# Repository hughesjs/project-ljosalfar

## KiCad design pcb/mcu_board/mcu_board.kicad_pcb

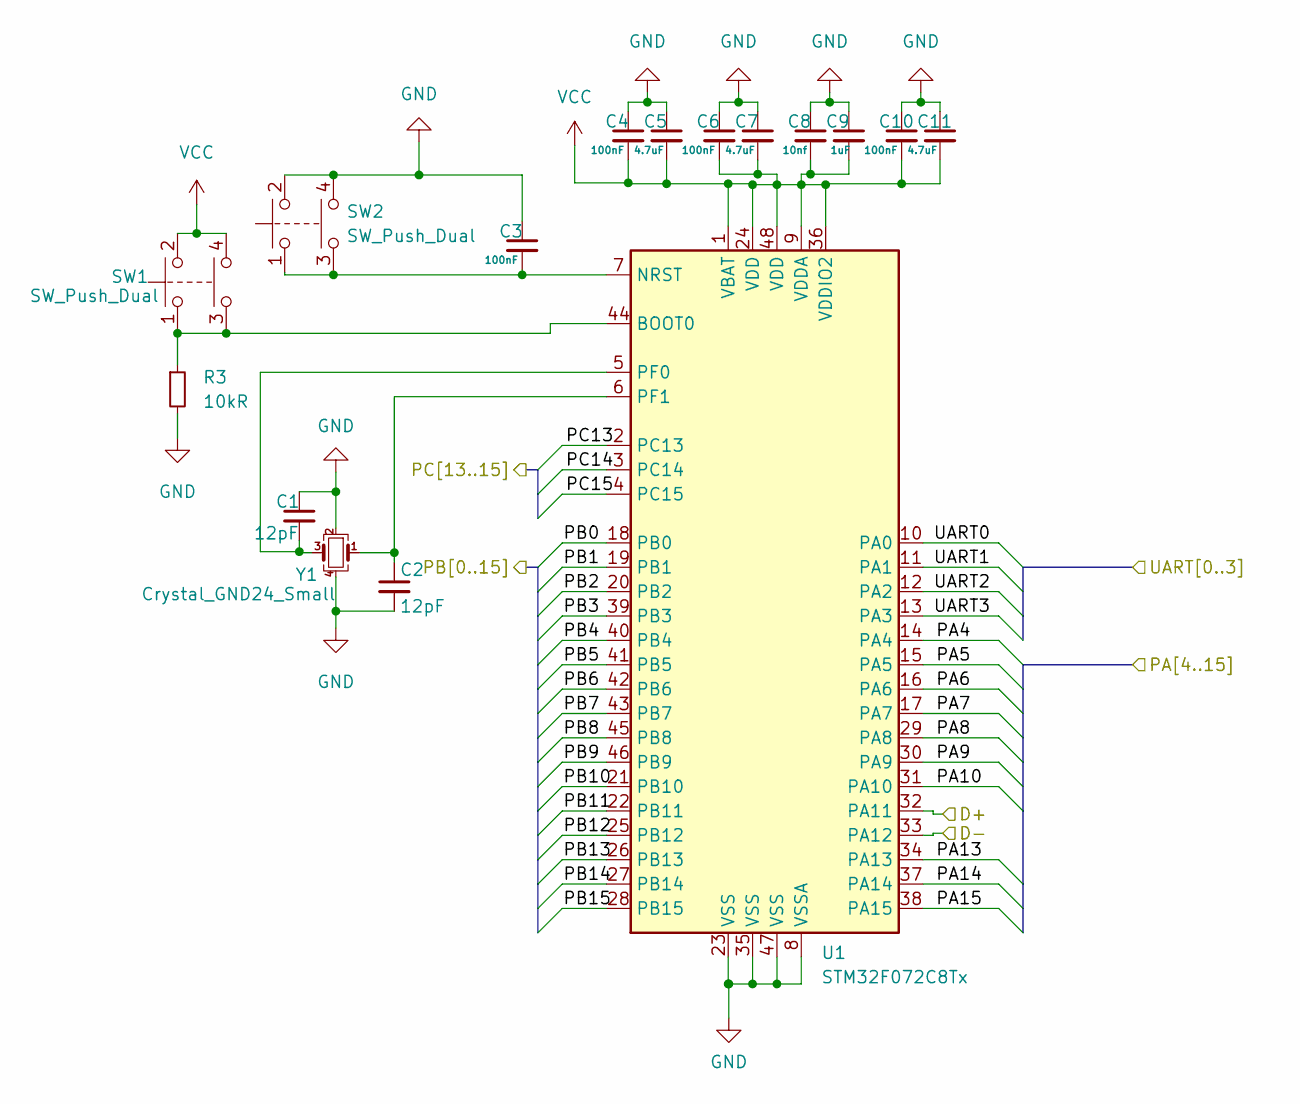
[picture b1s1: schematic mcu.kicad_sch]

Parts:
C1, C2: 12pF; C_0402_1005Metric
C3, C4, C6, C10: 100nF; C_0402_1005Metric
C5, C7, C11: 4.7uF; C_0603_1608Metric
C8: 10nf; C_0402_1005Metric
C9: 1uF; C_0603_1608Metric
R3: 10kR; R_0603_1608Metric
SW1, SW2: SW_Push_Dual; SW_TS-1187A-B-A-B
U1: STM32F072C8Tx; LQFP-48_7x7mm_P0.5mm
Y1: Crystal_GND24_Small; Crystal_SMD_3225-4Pin_3.2x2.5mm

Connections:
/USB_IN/D+: U1.32 (PA11); also elsewhere on the board
/USB_IN/D-: U1.33 (PA12); also elsewhere on the board
/mcu/PA4: U1.14 (PA4)
/mcu/PA5: U1.15 (PA5)
/mcu/PA6: U1.16 (PA6)
/mcu/PA7: U1.17 (PA7)
/mcu/PA8: U1.29 (PA8)
/mcu/PA9: U1.30 (PA9)
/mcu/PA10: U1.31 (PA10)
/mcu/PA13: U1.34 (PA13)
/mcu/PA14: U1.37 (PA14)
/mcu/PA15: U1.38 (PA15)
/mcu/PB0: U1.18 (PB0)
/mcu/PB1: U1.19 (PB1)
/mcu/PB2: U1.20 (PB2)
/mcu/PB3: U1.39 (PB3)
/mcu/PB4: U1.40 (PB4)
/mcu/PB5: U1.41 (PB5)
/mcu/PB6: U1.42 (PB6)
/mcu/PB7: U1.43 (PB7)
/mcu/PB8: U1.45 (PB8)
/mcu/PB9: U1.46 (PB9)
/mcu/PB10: U1.21 (PB10)
/mcu/PB11: U1.22 (PB11)
/mcu/PB12: U1.25 (PB12)
/mcu/PB13: U1.26 (PB13)
/mcu/PB14: U1.27 (PB14)
/mcu/PB15: U1.28 (PB15)
/mcu/PC13: U1.2 (PC13)
/mcu/PC14: U1.3 (PC14)
/mcu/PC15: U1.4 (PC15)
/mcu/UART0: U1.10 (PA0)
/mcu/UART1: U1.11 (PA1)
/mcu/UART2: U1.12 (PA2)
/mcu/UART3: U1.13 (PA3)
GND: C1.1, C2.2, C3.1, C4.1, C5.1, C6.1, C7.1, C8.1, C9.1, C10.1, C11.1, R3.2, SW2.2, SW2.4, U1.8 (VSSA), U1.23 (VSS), U1.35 (VSS), U1.47 (VSS), Y1.2, Y1.4; also elsewhere on the board
unnamed: C1.2, U1.5 (PF0), Y1.3
unnamed: C2.1, U1.6 (PF1), Y1.1
unnamed: C3.2, SW2.1, SW2.3, U1.7 (NRST)
unnamed: R3.1, SW1.1, SW1.3, U1.44 (BOOT0)
VCC: C4.2, C5.2, C6.2, C7.2, C8.2, C9.2, C10.2, C11.2, SW1.2, SW1.4, U1.1 (VBAT), U1.9 (VDDA), U1.24 (VDD), U1.36 (VDDIO2), U1.48 (VDD); also elsewhere on the board

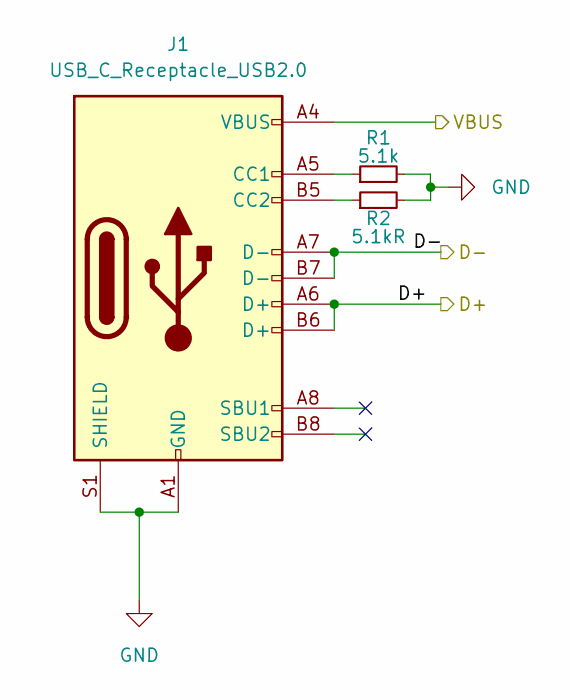
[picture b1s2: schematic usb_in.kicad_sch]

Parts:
J1: USB_C_Receptacle_USB2.0; USB_C_Receptacle_HRO_TYPE-C-31-M-12
R1: 5.1k; R_0603_1608Metric
R2: 5.1kR; R_0603_1608Metric

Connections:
/USB_IN/D+: J1.A6 (D+), J1.B6 (D+); also elsewhere on the board
/USB_IN/D-: J1.A7 (D-), J1.B7 (D-); also elsewhere on the board
/USB_IN/VBUS: J1.A4 (VBUS), J1.A9 (VBUS), J1.B4 (VBUS), J1.B9 (VBUS); also elsewhere on the board
GND: J1.A1 (GND), J1.A12 (GND), J1.B1 (GND), J1.B12 (GND), J1.S1 (SHIELD), R1.2, R2.2; also elsewhere on the board
unnamed: J1.A5 (CC1), R1.1
unnamed: J1.B5 (CC2), R2.1

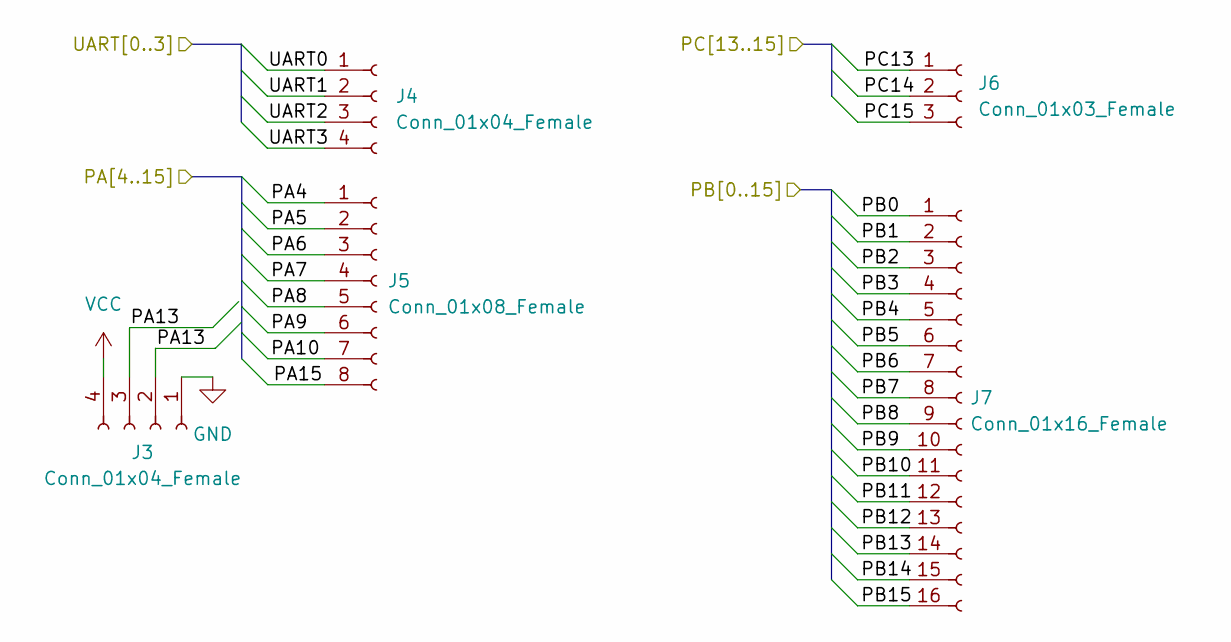
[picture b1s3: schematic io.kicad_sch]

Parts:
J3, J4: Conn_01x04_Female; PinHeader_1x04_P2.54mm_Vertical
J5: Conn_01x08_Female; PinHeader_1x08_P2.54mm_Vertical
J6: Conn_01x03_Female; PinHeader_1x03_P2.54mm_Vertical
J7: Conn_01x16_Female; PinHeader_1x16_P2.54mm_Vertical

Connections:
/io/PA4: J5.1
/io/PA5: J5.2
/io/PA6: J5.3
/io/PA7: J5.4
/io/PA8: J5.5
/io/PA9: J5.6
/io/PA10: J5.7
/io/PA13: J3.2, J3.3
/io/PA15: J5.8
/io/PB0: J7.1
/io/PB1: J7.2
/io/PB2: J7.3
/io/PB3: J7.4
/io/PB4: J7.5
/io/PB5: J7.6
/io/PB6: J7.7
/io/PB7: J7.8
/io/PB8: J7.9
/io/PB9: J7.10
/io/PB10: J7.11
/io/PB11: J7.12
/io/PB12: J7.13
/io/PB13: J7.14
/io/PB14: J7.15
/io/PB15: J7.16
/io/PC13: J6.1
/io/PC14: J6.2
/io/PC15: J6.3
/io/UART0: J4.1
/io/UART1: J4.2
/io/UART2: J4.3
/io/UART3: J4.4
GND: J3.1; also elsewhere on the board
VCC: J3.4; also elsewhere on the board

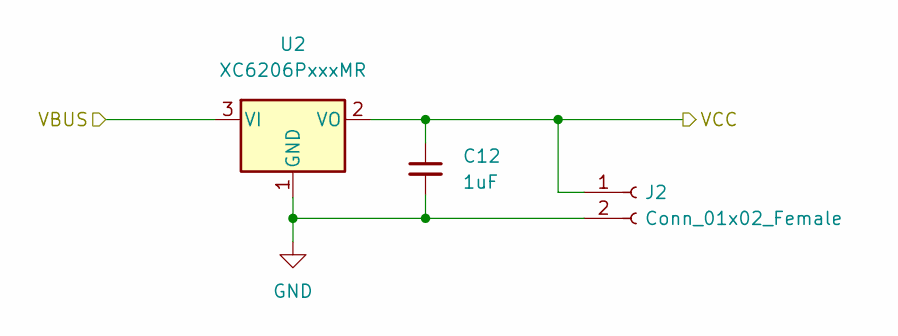
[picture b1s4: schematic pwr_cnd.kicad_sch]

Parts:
C12: 1uF; C_0603_1608Metric
J2: Conn_01x02_Female; PinHeader_1x02_P2.54mm_Vertical
U2: XC6206PxxxMR; SOT-23

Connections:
/USB_IN/VBUS: U2.3 (VI); also elsewhere on the board
GND: C12.2, J2.2, U2.1 (GND); also elsewhere on the board
VCC: C12.1, J2.1, U2.2 (VO); also elsewhere on the board

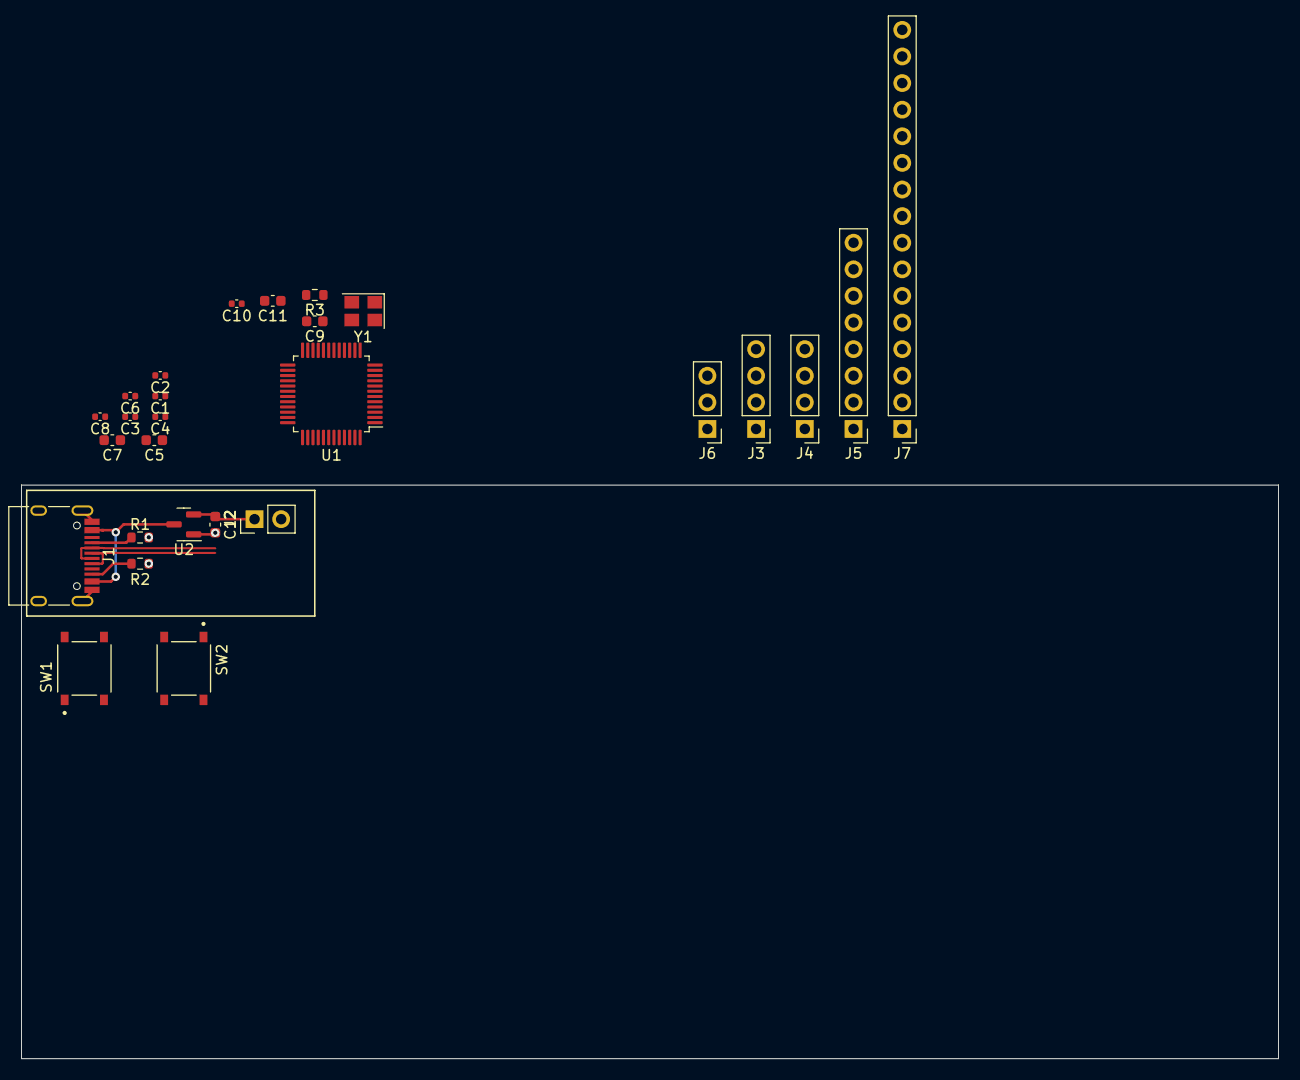
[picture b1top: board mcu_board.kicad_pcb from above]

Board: 2 copper layers, 120.0 x 54.8 mm, 27 parts (0 on the bottom side), 12 nets.

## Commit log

2022-09-17 First Pass Schematic
    First pass at the MCU Schematic
2022-09-17 Reworked schematic to use busses
2022-09-18 Started implementing USB and DAPLink
2022-09-18 Swapped from DAPLink to UART + SWD
2022-09-18 Pre-change of MCU
2022-09-18 First pass of complete design with PCB routed
2022-09-18 Updated routing
2022-09-19 Reworked PCB based on review
2022-09-19 Ready to BOM
2022-09-19 Submitted to JLCPCB
2022-09-20 Tidied up repo
2022-09-29 Rebuilt Schematic in KiCAD
2022-09-30 Fully annotated board
2022-10-01 Kicadification complete, not bothering to make the PCB though because it's about to get integrated onto the keyboard anyway
2022-10-01 Moved some stuff about
